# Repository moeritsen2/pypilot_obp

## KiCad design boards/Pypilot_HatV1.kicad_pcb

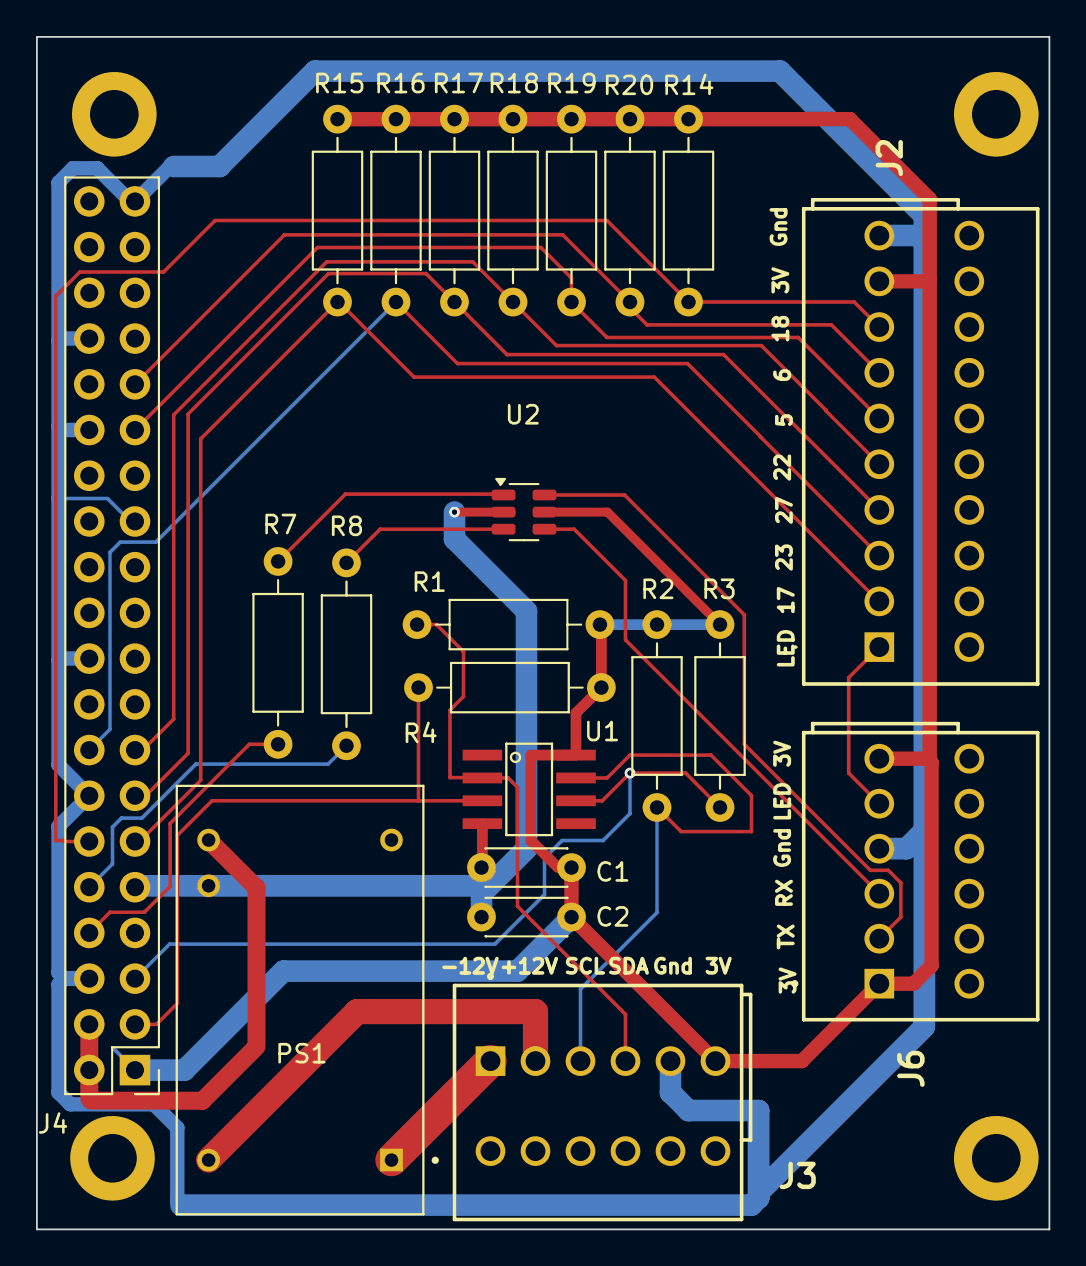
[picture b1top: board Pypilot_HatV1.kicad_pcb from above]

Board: 2 copper layers, 56.2 x 66.2 mm, 22 parts (0 on the bottom side), 23 nets.

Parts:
C1: 0.1uF; C_Disc_D4.3mm_W1.9mm_P5.00mm
C2: 1yF; C_Disc_D4.3mm_W1.9mm_P5.00mm
J2: Con Bedien2; 218510
J3: IMU; 218106
J4: Con to RPI; PinHeader_2x20_P2.54mm_Vertical
J6: Serial_Motor_controller; 218106
PS1: TEL_15-1211N; CONV_TEL_15-1211N
R1, R2: 430; R_Axial_DIN0207_L6.3mm_D2.5mm_P10.16mm_Horizontal
R3, R4: 4k7; R_Axial_DIN0207_L6.3mm_D2.5mm_P10.16mm_Horizontal
R7, R8: 2.4K; R_Axial_DIN0207_L6.3mm_D2.5mm_P10.16mm_Horizontal
R14, R15, R16, R17, R18, R19, R20: 47k; R_Axial_DIN0207_L6.3mm_D2.5mm_P10.16mm_Horizontal
U1: P82B715; SO8
U2: USBLC6-2SC6; SOT-23-6

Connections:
+3.3VP: C1.1, C2.1, J2.17 (9.1), J3.11 (6.1), J4.1, J4.17, J6.1 (1.1), J6.11 (6.1), R1.1, R2.1, R3.1, R4.1, R14.1, R15.1, R16.1, R17.1, R18.1, R19.1, R20.1, U1.8 (Vcc), U2.5 (VBUS)
+5V: J4.2, J4.4, PS1.9 (+VOUT)
+BATT: J3.3 (2.1), PS1.16 (+VIN)
/IMU_SCL: J3.5 (3.1), R2.2, U1.7 (Ly)
/IMU_SDA: J3.7 (4.1), R1.2, U1.2 (Lx)
/RX_in: R8.2, U2.3 (I/O2)
/SCL: J4.5, R3.2, U1.6 (Sy)
/SDA: J4.3, R4.2, U1.3 (Sx)
/SERIAL_RX: J4.10, R8.1
/SERIAL_TX: J4.8, R7.1
/Serial_RX_Motor: J6.3 (2.1), U2.6 (I/O1)
/Serial_TX_Motor: J6.5 (3.1), U2.4 (I/O2)
/TX_in: R7.2, U2.1 (I/O1)
GND: C1.2, C2.2, J2.19 (10.1), J3.9 (5.1), J4.6, J4.9, J4.14, J4.20, J4.25, J4.30, J4.34, J4.39, J6.7 (4.1), PS1.10 (-VOUT), U1.4 (GND), U2.2 (GND)
GND1: J3.1 (1.1), PS1.1 (-VIN)
KP_Auto: J2.3 (2.1), J4.11, R15.2
KP_Bb2: J2.7 (4.1), J4.13, R17.2
KP_Bb10: J2.11 (6.1), J4.29, R19.2
KP_Mode: J2.15 (8.1), J4.12, R14.2
KP_Stb2: J2.9 (5.1), J4.15, R18.2
KP_Stb10: J2.13 (7.1), J4.31, R20.2
KP_Tack: J2.5 (3.1), J4.16, R16.2
SLKLED: J2.1 (1.1), J6.9 (5.1)

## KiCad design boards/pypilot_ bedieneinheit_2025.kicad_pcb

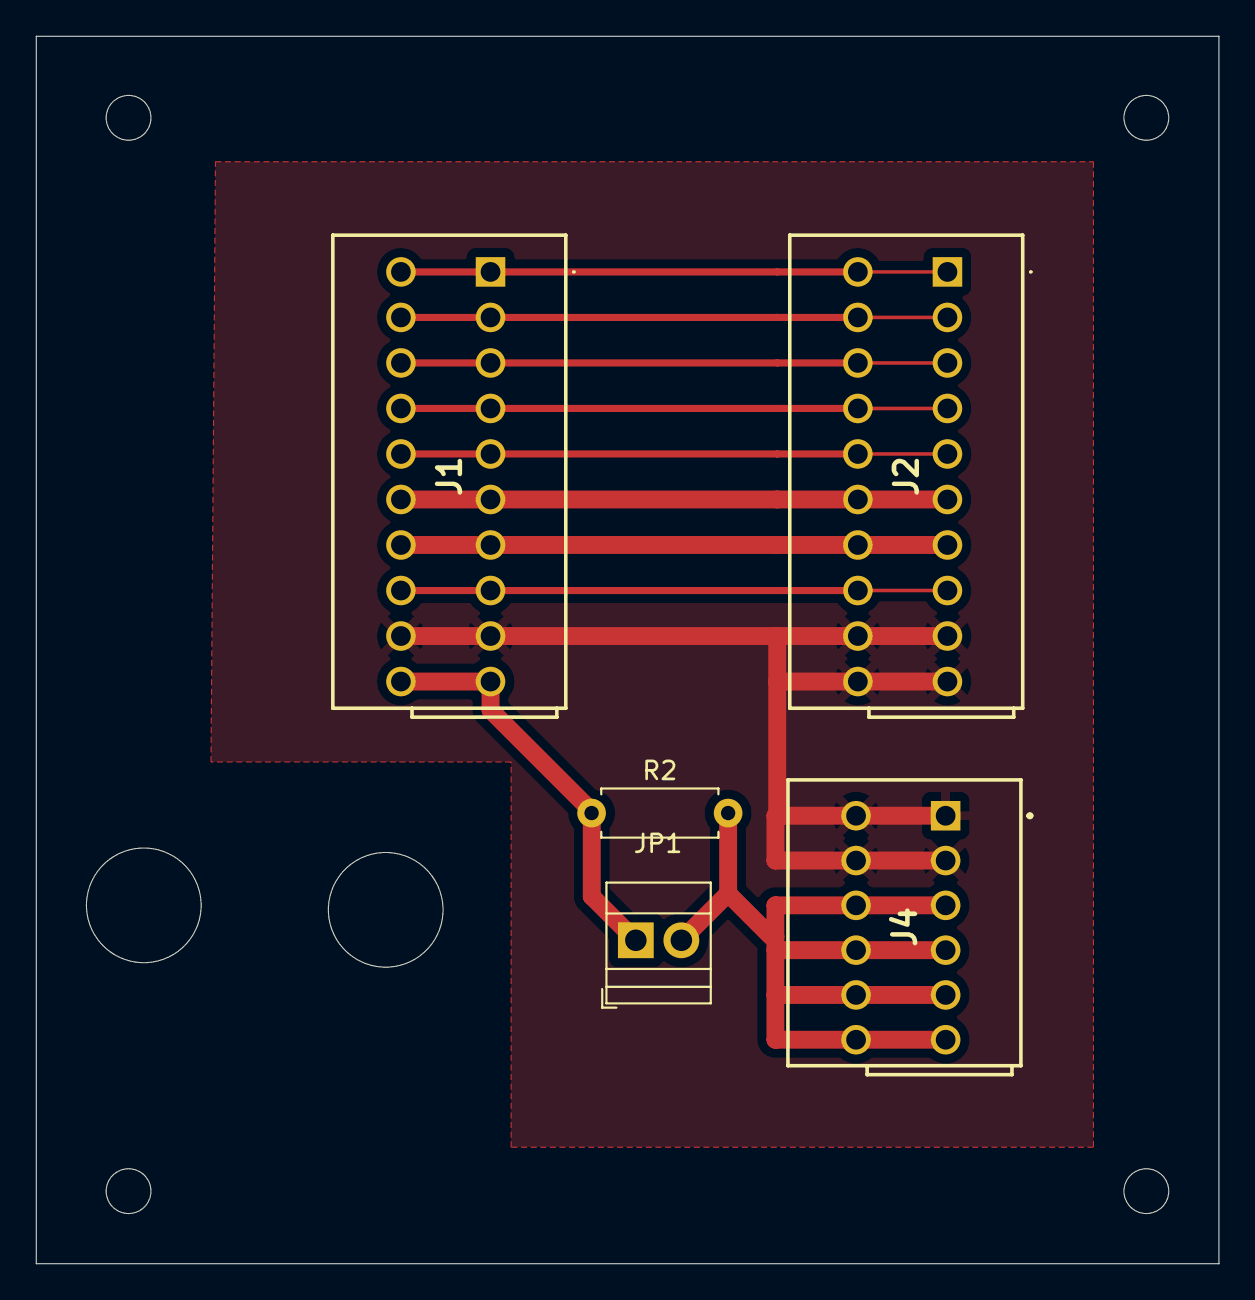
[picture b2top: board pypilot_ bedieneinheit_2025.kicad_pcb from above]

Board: 2 copper layers, 66.0 x 68.5 mm, 5 parts (0 on the bottom side), 11 nets.

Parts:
J1, J2: 218-510; 218510
J4: 218-106; 218106
JP1: Jumper_2_Open; TerminalBlock_Xinya_XY308-2.54-2P_1x02_P2.54mm_Horizontal
R2: 220; R_Axial_DIN0207_L6.3mm_D2.5mm_P7.62mm_Horizontal

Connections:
3.3V: J4.5 (3.1), J4.6 (3.2), J4.7 (4.1), J4.8 (4.2), J4.9 (5.1), J4.10 (5.2), J4.11 (6.1), J4.12 (6.2), JP1.2 (B), R2.2
Auto: J1.1 (1.1), J1.2 (1.2), J2.1 (1.1), J2.2 (1.2)
Bb2: J1.9 (5.1), J1.10 (5.2), J2.9 (5.1), J2.10 (5.2)
Bb10: J1.7 (4.1), J1.8 (4.2), J2.7 (4.1), J2.8 (4.2)
Gnd: J1.17 (9.1), J1.18 (9.2), J2.17 (9.1), J2.18 (9.2), J2.19 (10.1), J2.20 (10.2), J4.1 (1.1), J4.2 (1.2), J4.3 (2.1), J4.4 (2.2)
Gnd2: J1.13 (7.1), J1.14 (7.2), J2.13 (7.1), J2.14 (7.2)
LED: J1.11 (6.1), J1.12 (6.2), J2.11 (6.1), J2.12 (6.2)
unnamed: J1.19 (10.1), J1.20 (10.2), JP1.1 (A), R2.1
Reserve: J1.15 (8.1), J1.16 (8.2), J2.15 (8.1), J2.16 (8.2)
Stb2: J1.5 (3.1), J1.6 (3.2), J2.5 (3.1), J2.6 (3.2)
Stb10: J1.3 (2.1), J1.4 (2.2), J2.3 (2.1), J2.4 (2.2)

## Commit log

2025-01-24 Create dateien
2025-02-04 Initial documentation setup
